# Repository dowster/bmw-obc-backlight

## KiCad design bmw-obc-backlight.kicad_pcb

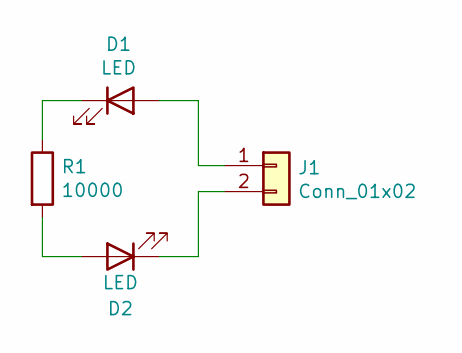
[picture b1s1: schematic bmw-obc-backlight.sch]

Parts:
D1, D2: LED; LED_0805_2012Metric_Castellated; JLC 0805
J1: Conn_01x02; TE_2Position_2.54mmPitch_Horizontal_Header
R1: 10000; R_1206_3216Metric_Pad1.30x1.75mm_HandSolder; JLC 1206

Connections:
unnamed: D1.1 (K), R1.1
unnamed: D1.2 (A), J1.1
unnamed: D2.1 (K), J1.2
unnamed: D2.2 (A), R1.2

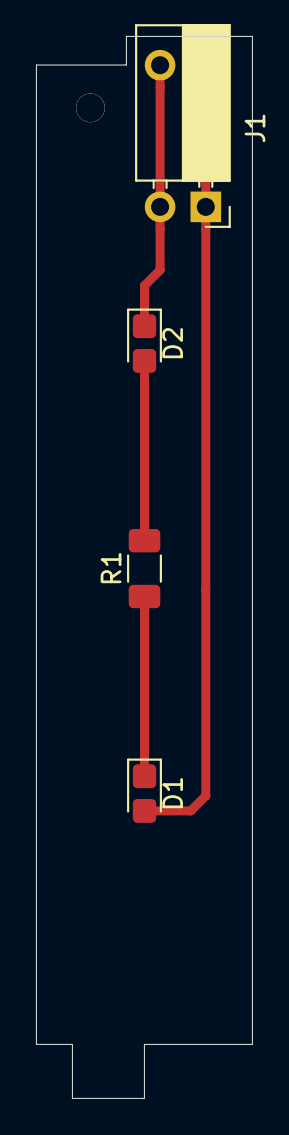
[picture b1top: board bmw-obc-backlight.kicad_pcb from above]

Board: 2 copper layers, 12.0 x 59.0 mm, 4 parts (0 on the bottom side), 4 nets.

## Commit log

2021-02-11 Rev 0 design
2021-03-06 Swapped resistor to SMT. There isn't enough space for a through hole unless it's between the LED legs.
2022-01-02 Swap to surface mount LEDs and add JLC manufacturing information
2022-01-03 Changes for ordering
2022-01-21 Update LED part number to white LED
